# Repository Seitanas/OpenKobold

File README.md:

# Open Kobold

**OpenKobold** is an OpenSource device to make your friends (or foes) go mad.  
The simplicity of psychological terror lies in the design -  
**OpenKobold** emits a high-pitch noise at a random time.  
Having a small-factor design (25x20mm) and a long silence period it is almost  
impossible to locate the device.  
And since MCU runs in-low power mode, it can last for  years.  
All hail mighty **OpenKobold**  
Have fun.  
Please don't kill each other...

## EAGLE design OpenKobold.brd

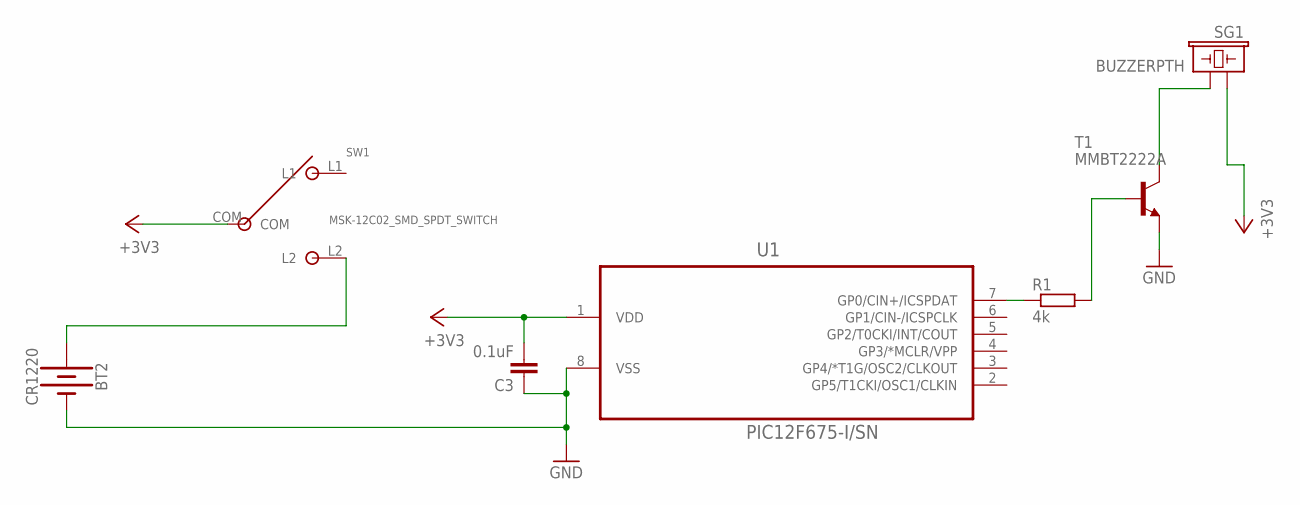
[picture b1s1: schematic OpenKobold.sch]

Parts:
BT2: CR1220; BATTCON_12MM
C3: 0.1uF; C0805
R1: 4k; R0805
SG1: BUZZERPTH; BUZZER-12MM
SW1: MSK-12C02_SMD_SPDT_SWITCH; MSK-12C02
T1: MMBT2222A; SOT23-BEC
U1: PIC12F675-I/SN; SOIC127P600X175-8N

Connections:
+3V3: C3.2, SG1.+ (1), SW1.COM, U1.1 (VDD)
GND: BT2.GND@1 (-), C3.1, T1.E, U1.8 (VSS)
unnamed: R1.2, T1.B
unnamed: SG1.- (2), T1.C
unnamed: R1.1, U1.7 (GP0/CIN+/ICSPDAT)
unnamed: BT2.PWR@1 (+), SW1.L2

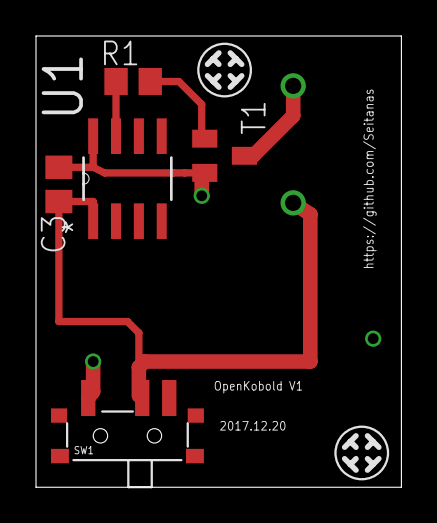
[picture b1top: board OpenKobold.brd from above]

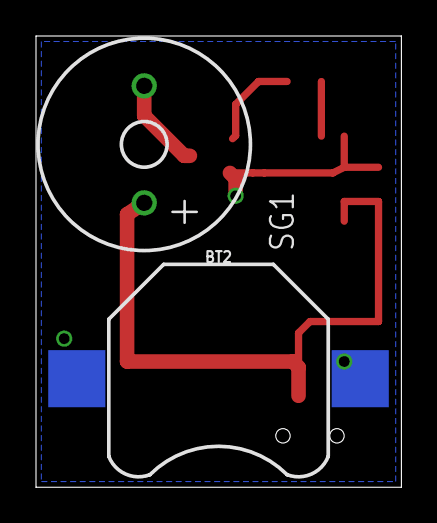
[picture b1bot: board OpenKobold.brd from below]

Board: 2 copper layers, 20.3 x 25.1 mm, 9 parts (2 on the bottom side), 6 nets.

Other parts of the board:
U$2, U$3: TADAS

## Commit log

2018-03-02 Updating info
2018-03-02 Adding eagle files
2018-03-02 Adding description
2018-03-02 Adding images
2018-03-02 Renaming file
2018-03-02 Adding images to README
2018-03-08 Adding part numbers to schematics
2018-07-02 Create LICENSE
